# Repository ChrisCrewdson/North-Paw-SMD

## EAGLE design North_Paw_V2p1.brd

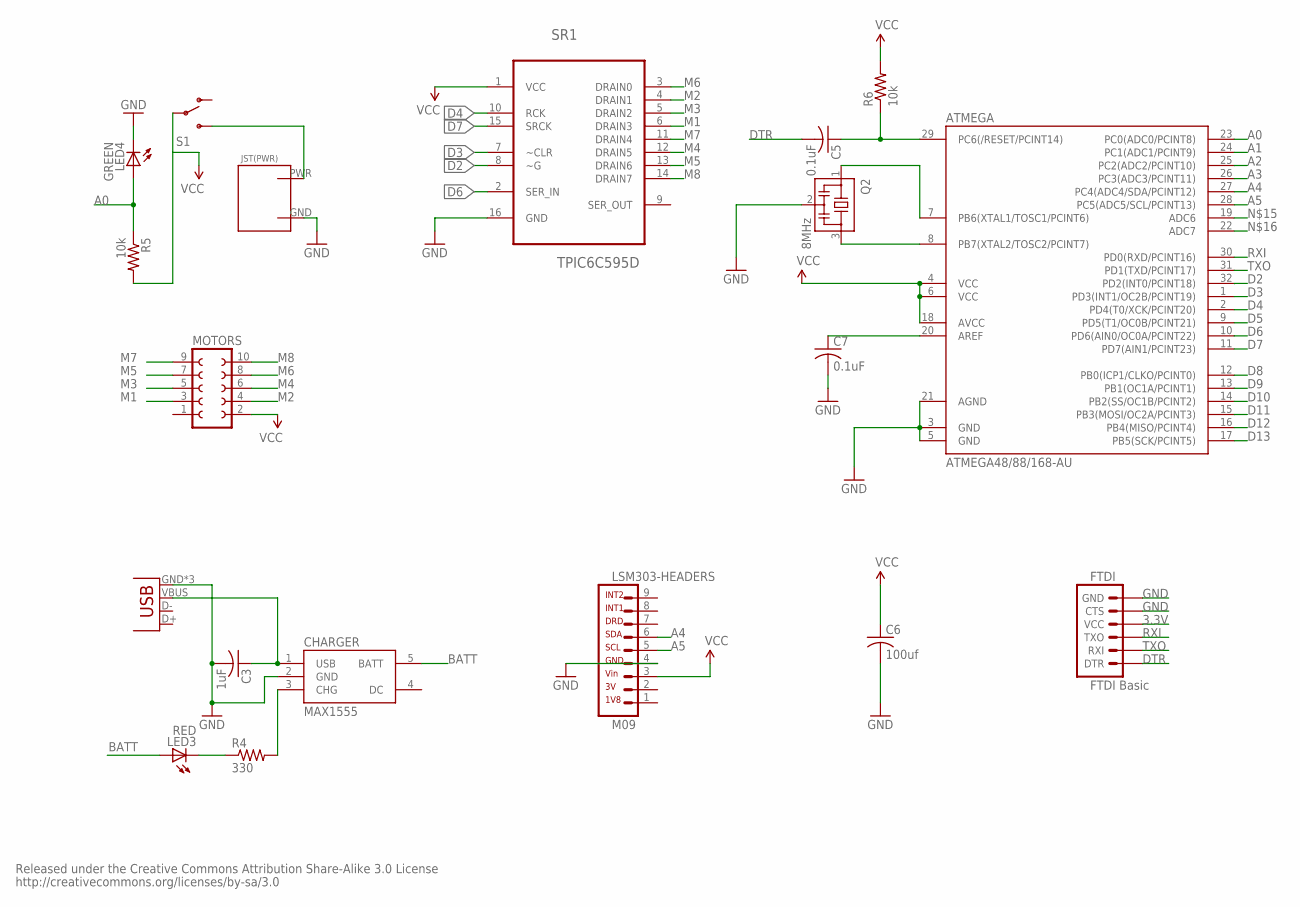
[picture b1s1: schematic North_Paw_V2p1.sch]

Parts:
ATMEGA: ATMEGA48/88/168-AU; TQFP32-08
C3: 1uF; C0805; MPN C0805C105K4RACTU
C5, C7: 0.1uF; C0805; MPN C0805C104K3RACTU
C6: 100uf; C0805; MPN TLCR107M004XTA
CHARGER: MAX1555; SOT23-5; MPN MAX1555EZK+T.
FTDI: FTDI Basic; 1X06
JP1: USB-MICROB
JST(PWR): S2B-PH-K-S; S4B-ZR
LED3: RED; CHIP-LED0805; MPN 150080RS75000
LED4: GREEN; CHIP-LED0805; MPN 150080GS75000
LSM303-HEADERS: M09; MA09-1W
MOTORS: FE05-2
Q2: 8MHz; CSTCR6M
R4: 330; R0805; MPN CRCW0805330RJNEA
R5, R6: 10k; R0805; MPN CRCW080510K0FKTA
S1: SWITCH-SPDT-SMD-A; SWITCH-SPST-SMD-A
SR1: TPIC6C595D; SOIC127P600X175-16N

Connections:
3.3V: ATMEGA.4 (VCC), ATMEGA.6 (VCC), ATMEGA.18 (AVCC), C6.1, FTDI.4 (VCC), LSM303-HEADERS.3, MOTORS.2, R5.2, R6.2, S1.2, SR1.1 (VCC)
A0: ATMEGA.23 (PC0(ADC0/PCINT8)), LED4.A, R5.1
A1: ATMEGA.24 (PC1(ADC1/PCINT9))
A2: ATMEGA.25 (PC2(ADC2/PCINT10))
A3: ATMEGA.26 (PC3(ADC3/PCINT11))
A4: ATMEGA.27 (PC4(ADC4/SDA/PCINT12)), LSM303-HEADERS.6
A5: ATMEGA.28 (PC5(ADC5/SCL/PCINT13)), LSM303-HEADERS.5
BATT: CHARGER.5 (BATT), LED3.A
D2: ATMEGA.32 (PD2(INT0/PCINT18)), SR1.8 (~G)
D3: ATMEGA.1 (PD3(INT1/OC2B/PCINT19)), SR1.7 (~CLR)
D4: ATMEGA.2 (PD4(T0/XCK/PCINT20)), SR1.10 (RCK)
D5: ATMEGA.9 (PD5(T1/OC0B/PCINT21))
D6: ATMEGA.10 (PD6(AIN0/OC0A/PCINT22)), SR1.2 (SER_IN)
D7: ATMEGA.11 (PD7(AIN1/PCINT23)), SR1.15 (SRCK)
D8: ATMEGA.12 (PB0(ICP1/CLKO/PCINT0))
D9: ATMEGA.13 (PB1(OC1A/PCINT1))
D10: ATMEGA.14 (PB2(SS/OC1B/PCINT2))
D11: ATMEGA.15 (PB3(MOSI/OC2A/PCINT3))
D12: ATMEGA.16 (PB4(MISO/PCINT4))
D13: ATMEGA.17 (PB5(SCK/PCINT5))
DTR: C5.2, FTDI.1 (DTR)
GND: ATMEGA.3 (GND), ATMEGA.5 (GND), ATMEGA.21 (AGND), C3.2, C6.2, C7.2, CHARGER.2 (GND), FTDI.5 (CTS), FTDI.6 (GND), JP1.GND, JP1.MT1 (GND), JP1.MT2 (GND), JST(PWR).GND, LED4.C, LSM303-HEADERS.4, Q2.2, SR1.16 (GND)
M1: MOTORS.3, SR1.6 (DRAIN3)
M2: MOTORS.4, SR1.4 (DRAIN1)
M3: MOTORS.5, SR1.5 (DRAIN2)
M4: MOTORS.6, SR1.12 (DRAIN5)
M5: MOTORS.7, SR1.13 (DRAIN6)
M6: MOTORS.8, SR1.3 (DRAIN0)
M7: MOTORS.9, SR1.11 (DRAIN4)
M8: MOTORS.10, SR1.14 (DRAIN7)
unnamed: ATMEGA.7 (PB6(XTAL1/TOSC1/PCINT6)), Q2.1
unnamed: ATMEGA.8 (PB7(XTAL2/TOSC2/PCINT7)), Q2.3
unnamed: ATMEGA.20 (AREF), C7.1
unnamed: JST(PWR).PWR, S1.3 (S)
unnamed: CHARGER.3 (CHG), R4.2
unnamed: LED3.C, R4.1
RESET: ATMEGA.29 (PC6(/RESET/PCINT14)), C5.1, R6.1
RXI: ATMEGA.30 (PD0(RXD/PCINT16)), FTDI.3 (TXO)
TXO: ATMEGA.31 (PD1(TXD/PCINT17)), FTDI.2 (RXI)
USB_VIN: C3.1, CHARGER.1 (USB), JP1.VBUS

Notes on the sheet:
Released under the Creative Commons Attribution Share-Alike 3.0 License
http://creativecommons.org/licenses/by-sa/3.0

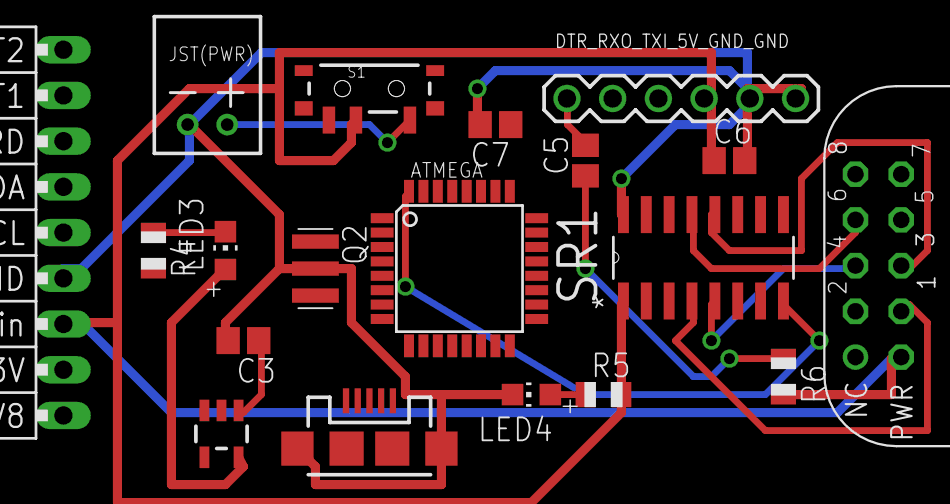
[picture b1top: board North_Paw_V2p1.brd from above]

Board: 2 copper layers, 19 parts (0 on the bottom side), 30 nets.

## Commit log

2013-12-17 Initial commit of existing files
2013-12-19 More smd and routing updates
2014-03-08 Initial checkin of TopoR

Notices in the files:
parts and their libraries:
SparkFun-Connectors: Licensing: CC v3.0 Share-Alike You are welcome to use this library for commercial purposes.
